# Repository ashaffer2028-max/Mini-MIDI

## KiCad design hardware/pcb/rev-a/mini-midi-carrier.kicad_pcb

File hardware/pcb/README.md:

# Initial PCB model — revision A

**Schematic and component placement draft. UNROUTED. Not for fabrication.**

This first model keeps the KB2040 module and puts three analog-control connectors plus four switch connectors on a provisional 90 × 60mm two-layer carrier. It preserves the active firmware and MIDI mappings. Read the [architecture, pin contract, sources and assumptions](DESIGN_NOTES.md) before editing or connecting hardware.

The preview shows component pads, placement and 18 pin-function silkscreen labels, not finished copper routing. Open the PCB in KiCad to see the unrouted connections.

## Open and edit

Open [mini-midi-carrier.kicad_pro](rev-a/mini-midi-carrier.kicad_pro) in **KiCad 9**. The project includes:

- [Native schematic](rev-a/mini-midi-carrier.kicad_sch) and [schematic preview](rev-a/previews/mini-midi-carrier.svg).
- [Native PCB](rev-a/mini-midi-carrier.kicad_pcb), local symbols and a socketed-module footprint with project-local library tables.
- [Auditable module pad map](rev-a/module-pin-map.json), original/source header IDs and coordinates.
- [Connectivity checker](rev-a/check_connectivity.py) and [recorded check reports](rev-a/checks/).

The module symbol abstracts the purchased board as passive connection pins. ERC does not analyze the module's internal regulator, USB circuit or RP2040. Carrier pad numbering is defined in the design notes and is not a physical KB2040 silkscreen numbering scheme.

## Checks recorded on 2026-11-15

| Check | Result | What it establishes |
| --- | --- | --- |
| Schematic ERC, KiCad 9.0.2 | 0 violations | Connected labels, no-connect flags and library references pass this model's rules |
| PCB DRC | 0 geometry violations; **20 unconnected items** | Placement is free of reported geometry violations; routing is incomplete |
| Schematic/PCB parity | 0 issues | Symbol references, footprints and pad nets correspond |
| Independent connectivity audit | Pass | All 26 module pad centers, 8 firmware assignments and 24 net membership sets match |
| Physical test / enclosure fit | Not performed | No fabrication or fit readiness claim |

Do not interpret the geometry result as a completed DRC pass: the 20 unrouted connections remain blockers. No Gerbers or drill package has been released.

## Recheck after edits

From the repository root:

```sh
kicad-cli sch erc --format json --units mm -o hardware/pcb/rev-a/checks/erc.json hardware/pcb/rev-a/mini-midi-carrier.kicad_sch
kicad-cli pcb drc --schematic-parity --format json --units mm -o hardware/pcb/rev-a/checks/drc.json hardware/pcb/rev-a/mini-midi-carrier.kicad_pcb
python3 hardware/pcb/rev-a/check_connectivity.py
```

Use the Python interpreter supplied with KiCad or one with `pcbnew` installed (the recorded audit used `/usr/bin/python3`). The audit generates a fresh temporary schematic netlist; it checks logical membership, not trace completion. Mismatches exit nonzero even under `python3 -O`; validation uses explicit checks rather than removable assertions. `--project-dir` and `--repo-root` let regression tests check temporary copies without touching the working design. Inspect report contents: the CLI commands above can produce reports while returning success even with reported violations.

## Before routing and fabrication

1. Confirm the actual KB2040 revision, socket geometry and header stack height with a 1:1 print and samples.
2. Establish enclosure internal clearance, USB plug space and mounting points; revise the provisional outline.
3. Finalize exact harness connectors and orientation labels. Confirm every control against the existing wiring table.
4. Route all nets on F.Cu/B.Cu, provide ground distribution and review return paths. Assess optional filtering using measured analog noise.
5. Run ERC, DRC including unconnected items and schematic parity again. Review clearances, fabrication rules, silkscreen, actual part drawings and assembly access before generating manufacturing outputs.

No boards or parts have been ordered, and the active firmware has not been modified by this contribution.

## Audit regression checks

With KiCad's Python interpreter, run from the repository root:

```sh
python3 -m unittest discover -s tests -p test_pcb_audit.py -v
```

These integration tests accept the current design and deliberately corrupt a copied module coordinate and firmware pin assignment. Both mismatches must fail in normal and optimized Python modes. Without `pcbnew` or `kicad-cli`, these tests are skipped; a skipped test is not PCB validation.

Reviewed 2026-11-15: [Python assertion behavior](https://docs.python.org/3/reference/simple_stmts.html#the-assert-statement) explains why `assert` is unsuitable as a mandatory audit check when optimized mode is permitted. KiCad check commands are documented in the [official CLI reference](https://docs.kicad.org/9.0/en/cli/cli.html).

## Header labels and harness checks

The front silkscreen now marks every control header pin: J1/J2/J3 show GND, A0/A1/A2 and +3V3; J4/J6/J7 show their digital input and GND; J5 shows D3, GND and D4. Numbers identify the carrier header pins, not the physical toggle's lug numbers. Labels reduce ambiguity but do not polarize the unkeyed connectors.

Before powering a completed assembly, verify each harness against the schematic with a continuity meter. The pot wiper must reach pin 2 and the other two pins must reach GND/+3V3. J5 pin 2 is common/GND; the switch itself must provide the specified center-off truth table. Do not use the label position to infer which way a cable housing is viewed. No harness or physical board has been tested here.

The project footprint table explicitly references the standard KiCad 9 connector library through `KICAD9_FOOTPRINT_DIR`, so checks do not depend on a preconfigured global footprint table. Install the standard KiCad libraries if that variable's directory is unavailable. Reviewed 2026-11-15 against the [KiCad PCB library documentation](https://docs.kicad.org/9.0/en/pcbnew/pcbnew.html).

## Paper-fit template and connector review (2026-11-16)

Open the [true-scale fit sheet](rev-a/previews/fit-template.svg) directly and print at **100% / actual size**, with fit-to-page disabled. GitHub's on-screen preview is not a scale reference. Verify the horizontal **100mm** and vertical **50mm** bars using a ruler; reject a print with either axis scaled incorrectly. This top view is not mirrored.

The sheet derives its provisional outline, all 44 drill centers/diameters and module F.Fab outline from the native board. It omits socket/header bodies, USB plug overhang, cable bends and mounting holes. The dashed module boundary is the bare PCB outline, not a clearance envelope. Paper fitting does not validate physical assembly or electrical operation. Follow the [connector fit review](CONNECTOR_REVIEW.md) for candidate parts, source drawings and unresolved stack decisions.

Regenerate after moving parts or editing the outline:

```sh
python3 hardware/pcb/rev-a/export_fit_template.py
```

Use KiCad's Python with `pcbnew`. The [exporter](rev-a/export_fit_template.py) records the source PCB SHA-256 in SVG metadata, uses millimeter page dimensions with a matching viewBox, and rejects unsupported outlines or a board too large for this sheet. No native design, pin assignment, routing or check report was changed by this paper template.

Desktop verification on 2026-11-16: all 44 SVG pad centers and drill radii match the native PCB, and page units/scale bars were checked numerically. The rendered sheet was visually inspected. All 26 existing desktop tests pass with KiCad Python. Fresh KiCad 9.0.2 checks report 0 ERC violations, 0 geometric DRC violations, 20 unconnected items and 0 schematic parity issues. These checks do not verify printer scaling or actual part/enclosure fit.

## Placement-independent audit (2026-11-18)

The module geometry check now uses KiCad's footprint-relative pad positions. Moving or rotating the complete front-side module no longer creates a false source-coordinate mismatch; moving one pad within the footprint still fails. Back-side mounting is rejected explicitly because this draft's mounting orientation has not been reviewed for a flipped module. This check does not approve a new placement: rerun DRC/parity, regenerate previews/fit sheets and review USB/enclosure clearance after moving parts.

Regression checks use temporary board copies at 90°, 180°, 270° and 37°, plus deliberately displaced pads and a flipped module. Both normal and optimized Python are checked. The committed board has not moved. Reviewed 2026-11-18 against the [official KiCad 9 PAD API](https://docs.kicad.org/doxygen-python-9.0/classpcbnew_1_1PAD.html), including inherited `GetFPRelativePosition()`.

## Fit-sheet USB direction (2026-11-19)

The fixed “USB faces left” annotation is replaced by a direction arrow transformed with the front-side KB2040 footprint. The module title and USB annotation move with it; the sheet rejects a missing, duplicate or back-side module rather than labeling an unreviewed mounting arrangement. The arrow indicates the USB end only: it is **not** the connector outline, plug overhang or a keepout.

The existing [pinned Adafruit board source](https://github.com/adafruit/Adafruit-KB2040-PCB/blob/b4160dcf4385ef2cc30e9652489328321720ee4b/Adafruit%20KB2040.brd) was rechecked on 2026-11-19: USB element X6 lies at Eagle y=8.89mm, on the module's west end. The exporter uses the existing 33.02 × 17.78mm bare-board convention. Rotation uses the [official KiCad 9 FOOTPRINT orientation API](https://docs.kicad.org/doxygen-python-9.0/classpcbnew_1_1FOOTPRINT.html); regression tests compare the arrow against the independently transformed module pad positions at 0°, 90°, 180°, 270° and 37°.

## Supported fit-sheet hole geometry (2026-11-19)

The sheet supports circular drilled holes only. The exporter now checks both drill dimensions and the KiCad drill-shape field before writing the SVG. Oblong slots or unequal drill dimensions raise an error instead of being silently shown as circles. A failed export leaves an existing sheet untouched; that old sheet is stale until a supported export succeeds. Always check the command exit status and source hash before using a sheet.

Tests check all 44 current pad centers/radii, physical SVG units, both scale bars, rotation behavior and rejection of slot geometry in temporary board copies. No native board or hole dimensions changed. API reference reviewed 2026-11-19: [KiCad 9 PAD drill size/shape methods](https://docs.kicad.org/doxygen-python-9.0/classpcbnew_1_1PAD.html). The regenerated current sheet and a rotated temporary example were visually inspected; no printer or physical fit check was performed.

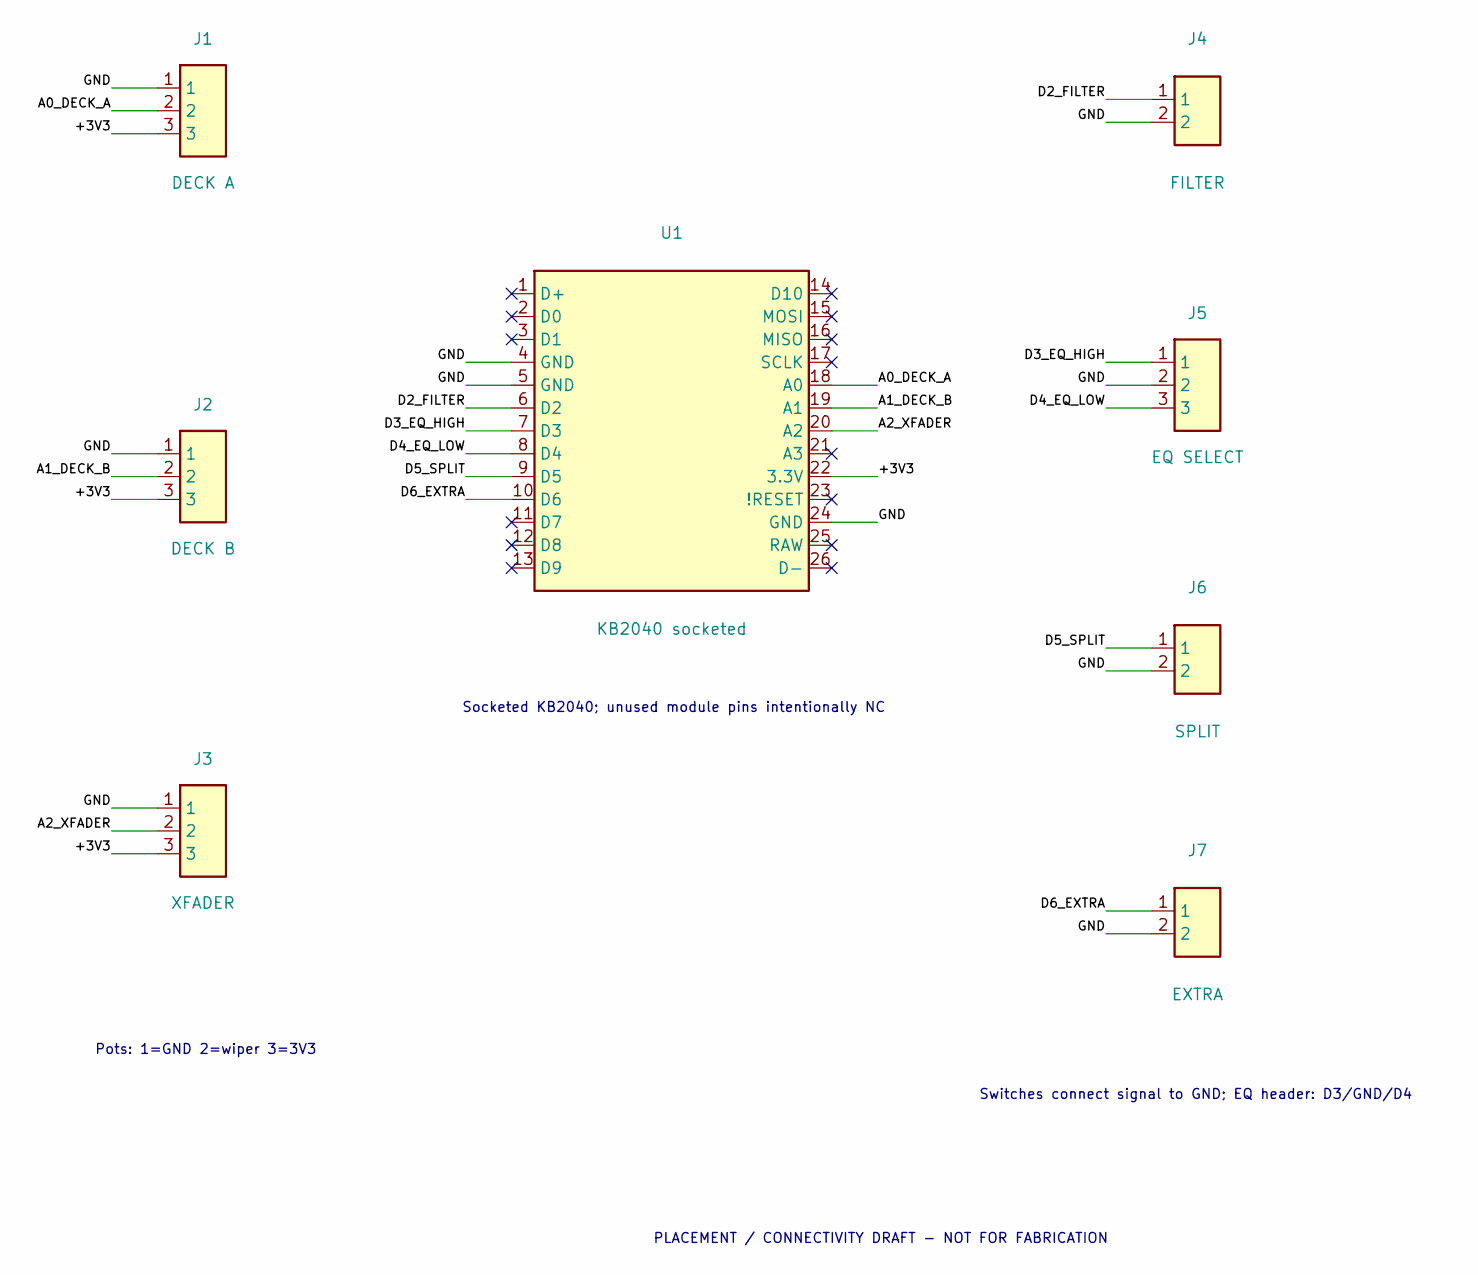
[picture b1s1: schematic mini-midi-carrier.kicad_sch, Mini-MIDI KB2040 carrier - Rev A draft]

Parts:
J1: DECK A; PinHeader_1x03_P2.54mm_Vertical
J2: DECK B; PinHeader_1x03_P2.54mm_Vertical
J3: XFADER; PinHeader_1x03_P2.54mm_Vertical
J4: FILTER; PinHeader_1x02_P2.54mm_Vertical
J5: EQ SELECT; PinHeader_1x03_P2.54mm_Vertical
J6: SPLIT; PinHeader_1x02_P2.54mm_Vertical
J7: EXTRA; PinHeader_1x02_P2.54mm_Vertical
U1: KB2040 socketed; KB2040_Socketed

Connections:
/+3V3: J1.3, J2.3, J3.3, U1.22 (3.3V)
/A0_DECK_A: J1.2, U1.18 (A0)
/A1_DECK_B: J2.2, U1.19 (A1)
/A2_XFADER: J3.2, U1.20 (A2)
/D2_FILTER: J4.1, U1.6 (D2)
/D3_EQ_HIGH: J5.1, U1.7 (D3)
/D4_EQ_LOW: J5.3, U1.8 (D4)
/D5_SPLIT: J6.1, U1.9 (D5)
/D6_EXTRA: J7.1, U1.10 (D6)
/GND: J1.1, J2.1, J3.1, J4.2, J5.2, J6.2, J7.2, U1.4 (GND), U1.5 (GND), U1.24 (GND)

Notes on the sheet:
Socketed KB2040; unused module pins intentionally NC
Pots: 1=GND 2=wiper 3=3V3
Switches connect signal to GND; EQ header: D3/GND/D4
PLACEMENT / CONNECTIVITY DRAFT - NOT FOR FABRICATION

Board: 2 copper layers, 8 parts (0 on the bottom side), 10 nets, no tracks yet.
